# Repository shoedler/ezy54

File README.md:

> Kailh Choc v1 pinks, Chosfox CFX

# ezy54
A 54-key, column-staggered, ortholinear, wireless split keyboard, inspired by ZSA Voyager and totem.
Designed for Choc-spacing (18mm horizontal, 17mm vertical) and 1350 Choc v1 or v2 switches.

## Impressions

> Left

> Carry Case

---

## Bill of materials

For one complete board - e.g. two halves - you'll need:

- 2 Promicro NRF52840
- 2x 12-pin 0.1" (2.54mm) Pitch **3.5mm tall** Pin headers, female. *I just ordered 40-pin lengths and cut them to size.* (optional, but highly recommended). 
- 54 1N4148W SOD-123 Diodes
- 54 Kailh Low-profile 1350 Hotswap Sockets
- 54 Keyswitches, Choc v1 or v2
- 54 Choc-spaced Keycaps, Choc v1 or v2 stems
- 2 EVQPUL02K Switches ($\to$ board reset button)
- 2 SSSS811101 Switches ($\to$ power switch)
- 2 701535 3.7v, 350mAh
- 2 JST PH 2.0 THT Sockets

For the case you'll need:

- Obviously, the printed case files. See section about printing below.
- 8x M2x6mm flathead screws
- 4x M2x14mm (or 12mm) flathead screws
- 12x M2x3mm Heat set inserts
- Optionally, some painters tape.

## Build guide

### PCB manufacturing

> PCB related files are located in the `kicad` directory.

Assuming you have ordered the parts and don't want to route the PCB yourself, there's premade gerber archive located at `kicad/gerber.zip` which you can use. I've used JLCPCB, default settings (1.6mm two layer PCB) and with the black solder mask.

### Printing the case

> Case files are located in the `stl` directory.

I used a Babulab A1 mini and default slicer settings (Bambustudio). Everything was printed in their PLA Matte.

#### What do I need to print?

You'll need at least:

- 2x `ezy54_switchplate_left.stl`, which is the plate that sits on the PCB and where the keyswitches are mounted into - I recommend using the provided 3mf files for that: `ezy54_switchplate_left.3mf` and `ezy54_switchplate_right.3mf`. That'll give you mirrored versions so you have the buildplate-finish texture on the same side for both halves. 
- 2x `ezy54_case_left.stl`, which is the case where the PCB gets mounted in - same story, use the provided 3mf files for that: `ezy54_case_left.3mf` and `ezy54_case_right.3mf`. That'll also give you mirrored versions for both halves. Theoretically, you don't **need** the case, but I strongly recommend it to provide a little bit of protection for the PCB. If you're working directly with the stl, then you'll have to mirror it. I suggest using the fuzzy skin setting (in Bambustudio: `Others > Special mode > Fuzzy skin`, use "Contour").

Optional:

- 1x `ezy54_carry_case.stl`, which is a Go60-ish carry shell for the ezy54. Use `ezy54_carry_case.3mf` for a basic. I did manage to print it without support, but there's a bit of luck involved - the 3mf file uses supports.

### Soldering

Since the PCB is reversible it can get confusing quick. All of the components **except the ProMicro headers and the JST Battery connector** are soldered to the backside of each half.

1. Solder diodes, kailh hotswap sockets, reset- and powerswitches on the backside of each half. **This is also the side were you bridge all of the solder-jumpers with solder** (8 for the Mcu, 2 for the Battery connector).
2. If you have ordered the female 3.5mm tall pin headers, solder them to the front. If not, direct solder the ProMicro to the frontside of the PCB. Also solder on the JST connector to the frontside.
3. Prep the ProMicro. They are usually delivered with male pin headers. You need to solder them flush in order to ensure the MCU will fit into the case. Here's the process I have used:

- left image: Push the pins, until they are almost flush with the plastic - a little (0.2mm) protrusion is ok. Ensure they are at the same depth.
- middle image: Insert the pins, MCU sits on the plastic, they act as the spacer for the insertion depth into the female header on the PCB. Tack-solder the outermost pins from the top (as shown in image).
- right image: Cut the pins flush with the MCU, then solder from the top. Do not use too much solder - we want to prevent the solder seeping through to the underside and forming a teardrop. Then, remove the plastic carefully - I have used a pair of flush cutters to gently lift it.

4. Mount the MCU to the header. Battery can wait for now.

> [!CAUTION]
> Before you continue it's a good idea to verify that there's no short between the JSTs +/- terminal as well as the ProMicros VCC and GND.

I suggest to load the firmware next and check that everything works before assembly.

### Loading the ZMK firmware

> Firmware related files consist of: config/, boards/, zephyr/ directories, as well as the build.yml file and the GitHub Actions workflow in .github/workflows.build.yml

Get the latest firmware from https://github.com/shoelder/ezy54/actions, select the latest run and scroll down to Artifacts - you'll be able to download the zip archive from there. If the last runs artifact is expired, just fork the repo and trigger a build.

> [!NOTE]
> There'll be two .uf2 files per half in the zip archive - a `de-ch` and an `en` version. This refers to the keycode locale that's been used. I myself require a swiss locale, but, to make the default firmware more useful for more people, I've added an english version too. You can check the keymaps out in the `config/boards/shields/ezy54` directory.

For each half:

1. Plug in the half to your device using a USB cable.
2. Press the reset button twice within 500ms - on my versions of the ProMicro, their red LED breaths gently once you've entered bootloader mode.
3. You'll see a `NICENANO` appear in your device tree. Simply drag and drop the **correct** firmware for the half your working on onto the mcu - it should eject itself automatically once the firmware is flashed.

> [!NOTE]
> If you run into trouble, there's also a `settings_reset` firmware provided in the archive. See [the ZMK troubleshooting guide](https://zmk.dev/docs/troubleshooting/connection-issues#reset-split-keyboard-procedure) on how to flash it.

### Assembly

1. Mount the battery to the frontside - I suggest a thin double-sided tape to keep it in place for easier assembly. It goes just below the MCU.
2. Mount the switchplate to the frontside - ensure it sits flush. The MCUs USB-C should be perfectly aligned to its cutout in the print.
3. Prep the lower cases halves by installing the heat set inserts.
4. Optional, but highly recommended for better sound: Cover the bottom sides of the PCBs with tape (I used masking tape). Apply the first layer quite firmly, such that it follows the contours of the hotswap sockets. You'll want to make sure that you extend the tape over the edges of the PCB. Apply at least 3 layers. In my experience anything beyond 5 layers of standard painters tape yields no further improvements. Also, it gets thick quick. Trace the PCB outline to the tape with a pen. Also, trace the screw holes. Remove the tape, and cut out the shape - make sure to inset the cut about 2-3mm, so the tape is not visible when everything is assembled. For the screw holes, cut a ~5x5mm square. Apply the tape. (There is a more detailed guile to the exact same process on the shoedler54 README: https://github.com/shoedler/shoedler54)
5. Assemble both halves and mount the screws.
6. Install the switches. Done!

---

## Modifying the ergogen config

The whole point of using ergogen, is to easily adapt the PCB to your liking. So give it a go!
Modifying the config will force you to reroute the PCB again. Though fear not - using [Freerouting](www.freerouting.app) this literally takes a minute to do (including adding freerouting to KiCad), provided you have KiCad >=8 and JRE >= 17 for Freerouting already installed.

> [!NOTE]
> To add the Freerouting KiCad integration, just follow [this](https://github.com/freerouting/freerouting/blob/master/docs/integrations.md) official guide.

> [!TIP]
> There is a local toolchain in [`tools/`](tools/README.md) that builds the config without
> ergogen.xyz and then checks it: case clearances, a pre-routing DRC on the generated board,
> STL/cross-section/point-probe inspection of the printed parts, and layered drawings. Start
> with `cd tools && npm run setup`, then `node tools/build.ts` and
> `node tools/drc-lite.ts out/pcbs/ezy54.kicad_pcb`. Its README also documents the
> footprint rotation convention that ergogen + KiCad make easy to get backwards.

1. Paste `config.yml` located in `/ergogen` into [ergogen.xyz](ergogen.xyz) and download the `ezy54.kicad_pcb` file.
2. Copy (and overwrite) `ezy54.kicad_pcb` to the `kicad` directory of this repository *(this part is only required if you intend to keep the source of this repository up to date - e.g. if you forked this)*
3. Open the PCB in KiCad (Standalone PCB editor suffices). Press `B` to fill the GND pours - zones come out of ergogen empty until KiCad calculates them once - then click on `Tools > External Plugins > Freerouting`
4. Let it rip. In my experience, the defaults of Freerouting suffice.

> [!IMPORTANT]
> Back in KiCad, run the DRC in `Inspect > Design Rule Checker`. I usually right click `> Ignore all 'Footprint not found in libraries' violations` to ignore missing ceoloide footprint warnings. This might leave you with some warnings which you need to manually resolve. For example, i usually get "Track has unconnected end", which is easily resolved by deleting the stub.

5. `File > Plot... > Generate Drill Files`, name the folder "gerber", then press `Generate` and close that popup. Press `Plot` back in the plot dialog. Done!

## References

- Flatfootfox' detailed design guide: https://flatfootfox.com/ergogen-part1-units-points/
- nickcoutsos Keymap-editor: https://nickcoutsos.github.io/keymap-editor/
- nickcoutsos Keymap-layout-tools: https://nickcoutsos.github.io/keymap-layout-tools/
- Joel Spadins zmk-locale-generator for the de-swiss keycode header: https://github.com/joelspadin/zmk-locale-generator
- ZMK guide on how to add a new shield: https://zmk.dev/docs/development/hardware-integration/new-shield
- More of my keyboards:
  - effiddy - a 50-key wireless split, inspired by totem: https://github.com/shoedler/effiddy
  - shoedler54 - a 54-key wireless split, inspired by ZSA Voyager and silakka54: https://github.com/shoedler/shoedler54

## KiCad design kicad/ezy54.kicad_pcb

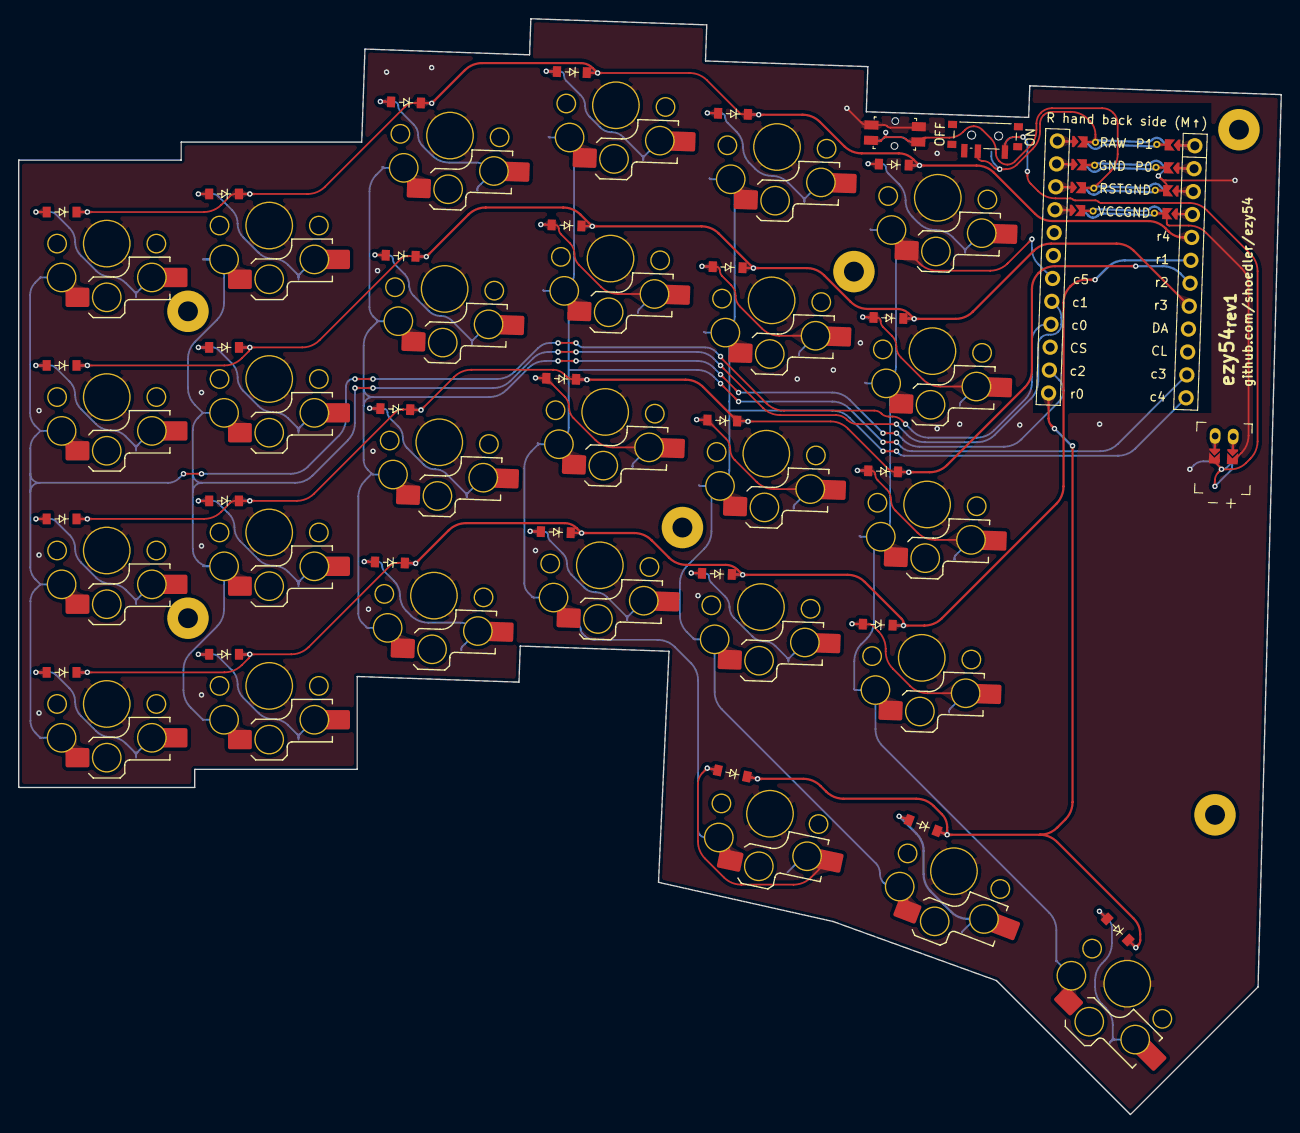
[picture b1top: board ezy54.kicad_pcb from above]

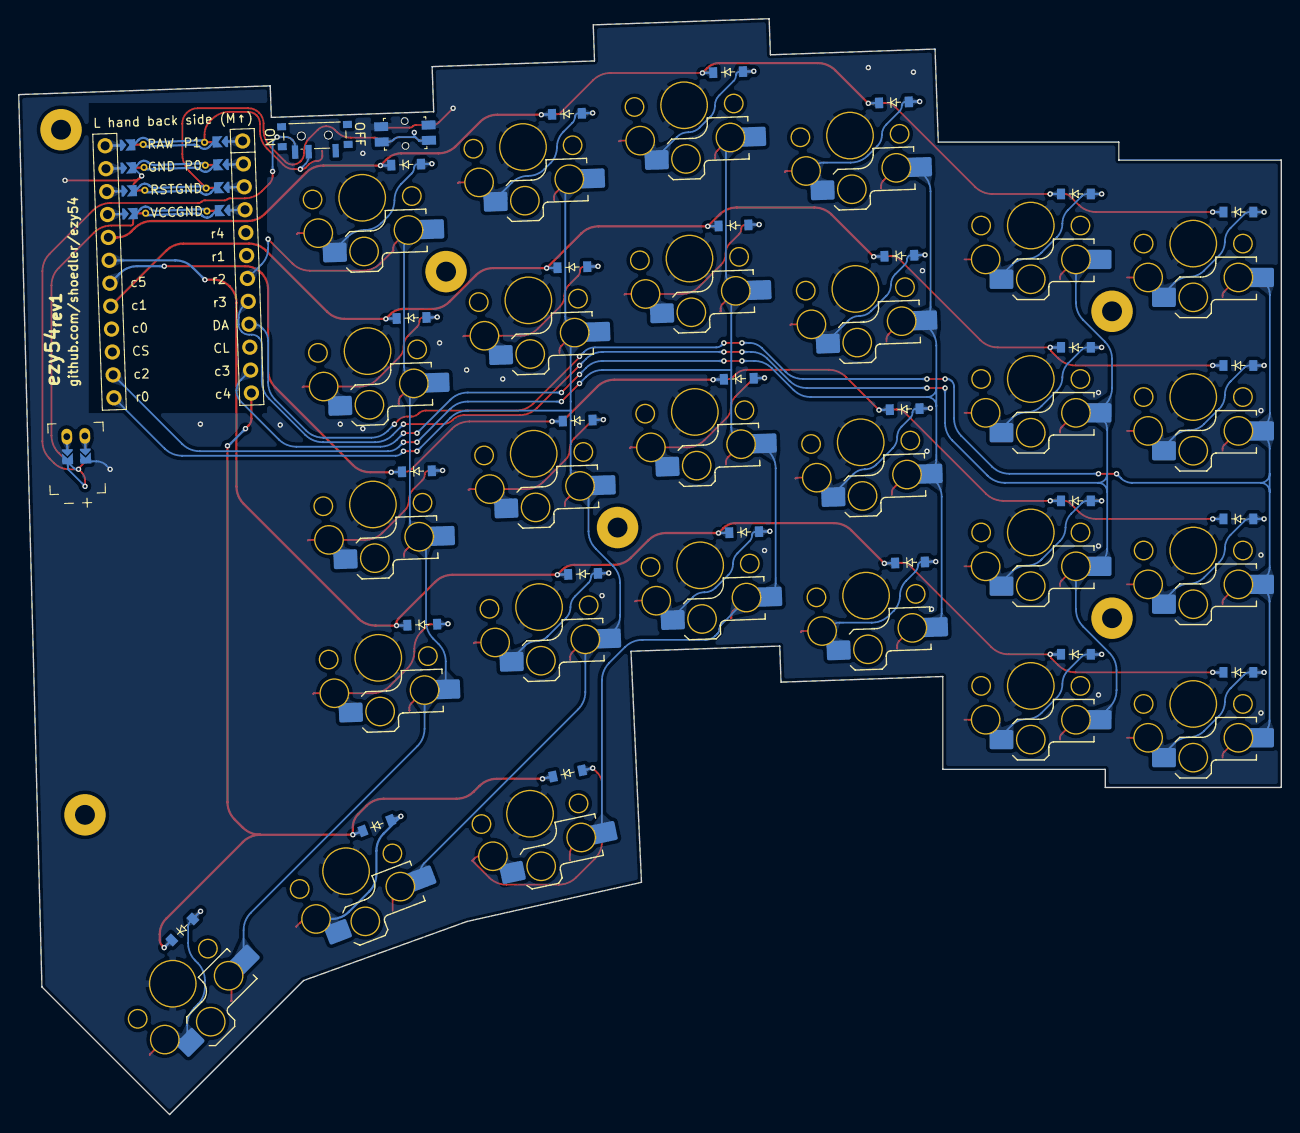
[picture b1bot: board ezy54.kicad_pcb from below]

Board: 2 copper layers, 139.9 x 121.4 mm, 64 parts (27 on the bottom side), 44 nets.

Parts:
D1, D2, D3, D4, D5, D6, D7, D8, D9, D10, D11, D12, D13, D14, D15, D16, D17, D18, D19, D20, D21, D22, D23, D24, D25, D26, D27: diode_tht_sod123
JST1: battery_connector_jst_ph_2
MCU1: mcu_supermini_nrf52840
MH1, MH2, MH3, MH4, MH5, MH6: mounting_hole_npth
PWR1: power_switch_smd_side
RST1: reset_switch_smd_side
S1, S2, S3, S4, S5, S6, S7, S8, S9, S10, S11, S12, S13, S14, S15, S16, S17, S18, S19, S20, S21, S22, S23, S24, S25, S26, S27: switch_choc_v1_v2

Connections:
BAT_P: JST1.1, PWR1.1, PWR1.3
GND: JST1.2, MCU1.103, MCU1.104, MCU1.123, RST1.1, RST1.3
JST1_1: JST1.11, JST1.21, JST1.31
JST1_2: JST1.12, JST1.22, JST1.32
RAW: MCU1.124, PWR1.2
RST: MCU1.122, RST1.2, RST1.4
c0: MCU1.16, S1.2, S2.2, S3.2, S4.2
c0_r1: D1.2, S1.1
c0_r2: D2.2, S2.1
c0_r3: D3.2, S3.1
c0_r4: D4.2, S4.1
c1: MCU1.17, S5.2, S6.2, S7.2, S8.2
c1_r1: D5.2, S5.1
c1_r2: D6.2, S6.1
c1_r3: D7.2, S7.1
c1_r4: D8.2, S8.1
c2: MCU1.14, S9.2, S10.2, S11.2, S12.2
c2_r1: D9.2, S9.1
c2_r2: D10.2, S10.1
c2_r3: D11.2, S11.1
c2_r4: D12.2, S12.1
c3: MCU1.11, S13.2, S14.2, S15.2, S16.2, S25.2
c3_r0: D25.2, S25.1
c3_r1: D13.2, S13.1
c3_r2: D14.2, S14.1
c3_r3: D15.2, S15.1
c3_r4: D16.2, S16.1
c4: MCU1.12, S17.2, S18.2, S19.2, S20.2, S26.2
c4_r0: D26.2, S26.1
c4_r1: D17.2, S17.1
c4_r2: D18.2, S18.1
c4_r3: D19.2, S19.1
c4_r4: D20.2, S20.1
c5: MCU1.18, S21.2, S22.2, S23.2, S24.2, S27.2
c5_r0: D27.2, S27.1
c5_r1: D21.2, S21.1
c5_r2: D22.2, S22.1
c5_r3: D23.2, S23.1
c5_r4: D24.2, S24.1
r0: D25.1, D26.1, D27.1, MCU1.13
r1: D1.1, D5.1, D9.1, D13.1, D17.1, D21.1, MCU1.6
r2: D2.1, D6.1, D10.1, D14.1, D18.1, D22.1, MCU1.7
r3: D3.1, D7.1, D11.1, D15.1, D19.1, D23.1, MCU1.8
r4: D4.1, D8.1, D12.1, D16.1, D20.1, D24.1, MCU1.5
